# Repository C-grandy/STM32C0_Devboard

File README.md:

# STM32C0_Devboard
A devboard for the STM32C031

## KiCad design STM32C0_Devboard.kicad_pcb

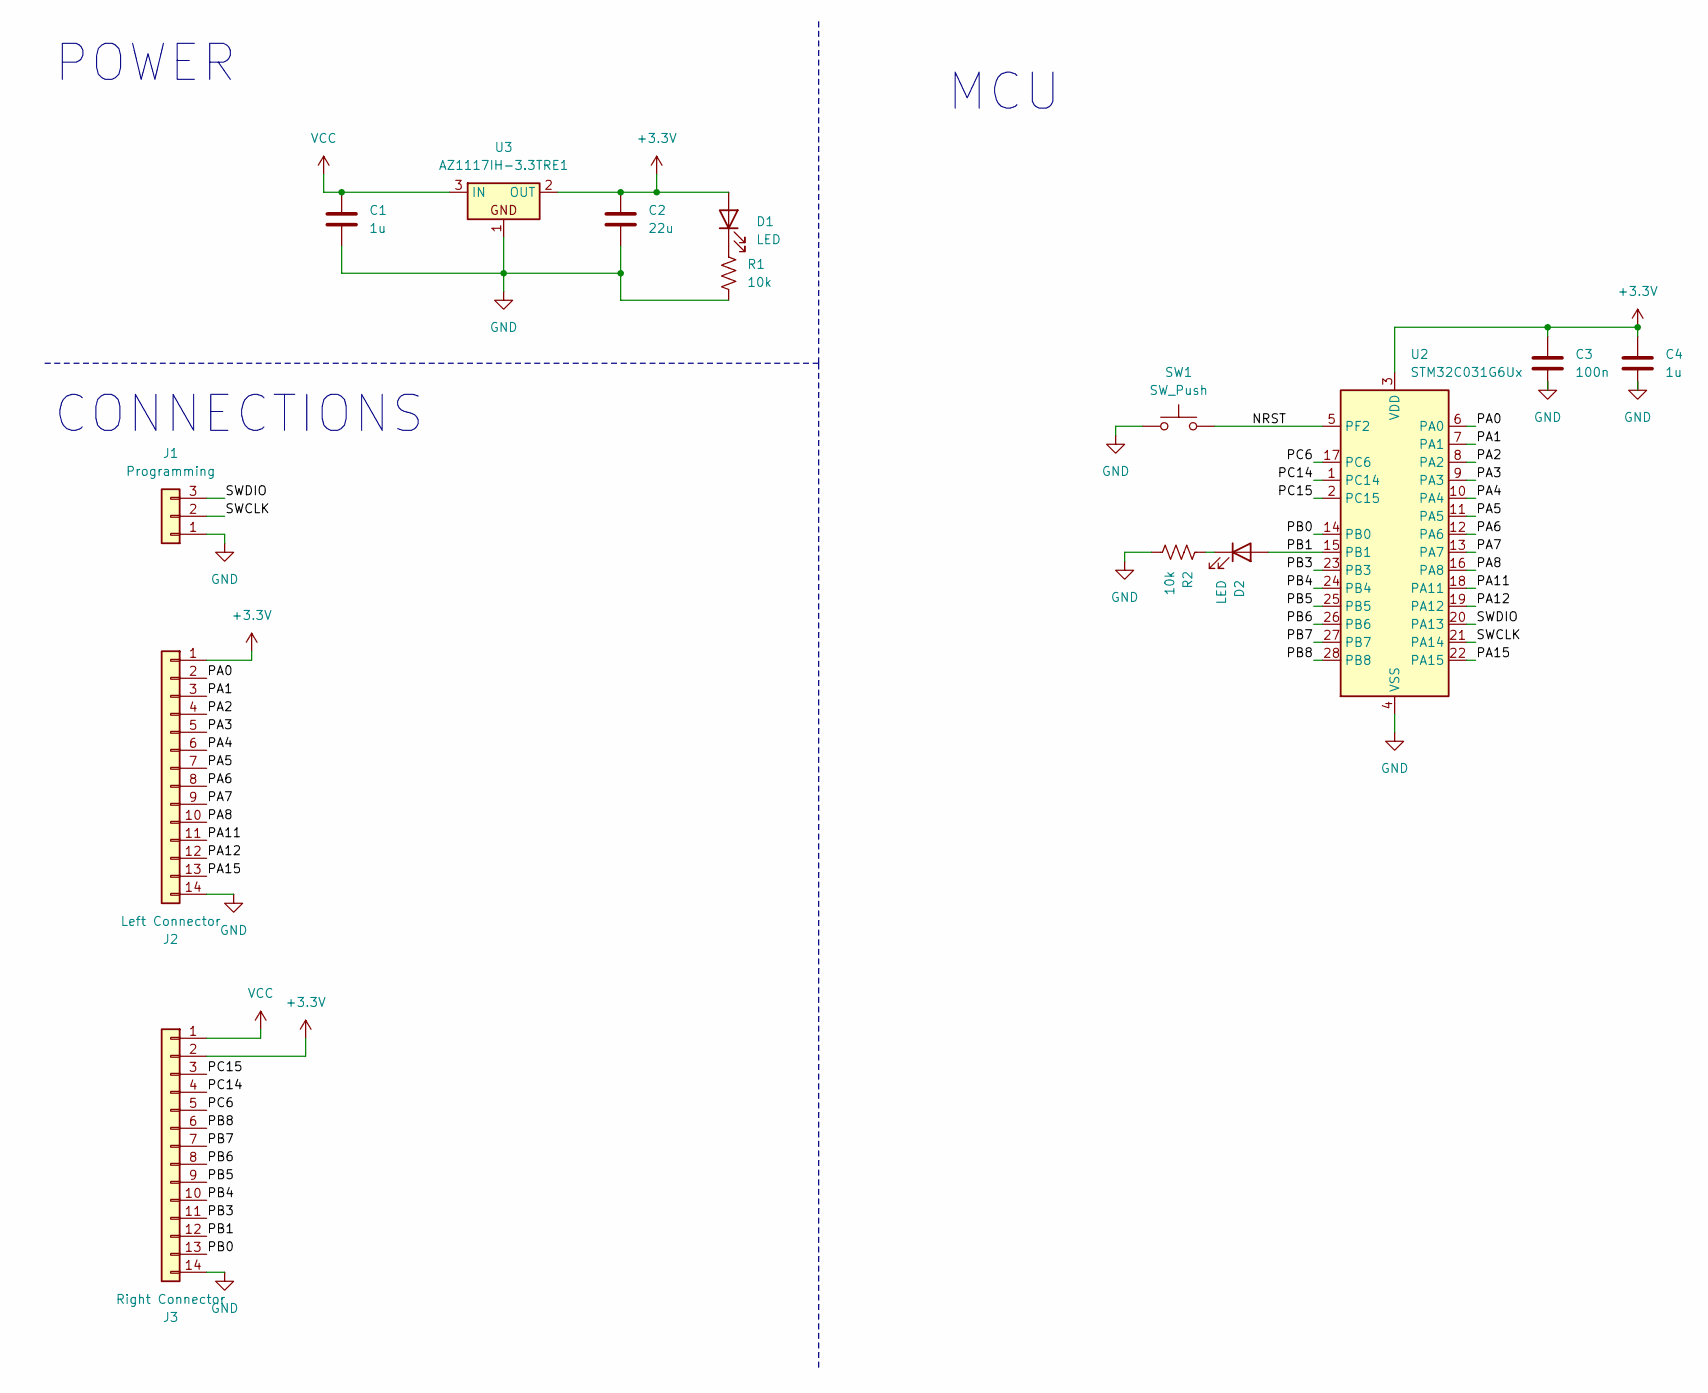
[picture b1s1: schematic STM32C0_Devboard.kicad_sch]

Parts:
C1, C4: 1u; C_0603_1608Metric
C2: 22u; C_0603_1608Metric
C3: 100n; C_0603_1608Metric
D1, D2: LED; LED_0603_1608Metric
J1: Programming; PinHeader_1x03_P2.54mm_Horizontal
J2: Left Connector; PinHeader_1x14_P2.54mm_Vertical
J3: Right Connector; PinHeader_1x14_P2.54mm_Vertical
R1, R2: 10k; R_0603_1608Metric
SW1: SW_Push; SW_Push_SPST_NO_Alps_SKRK; Part # PTS526SK15SMTR2 LFS
U2: STM32C031G6Ux; QFN-28_4x4mm_P0.5mm
U3: AZ1117IH-3.3TRE1; SOT-223-3_TabPin2

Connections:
+3.3V: C2.1, C3.1, C4.1, D1.2 (A), J2.1, J3.2, U2.3 (VDD), U3.2 (OUT)
/NRST: SW1.2, U2.5 (PF2)
/PA0: J2.2, U2.6 (PA0)
/PA1: J2.3, U2.7 (PA1)
/PA2: J2.4, U2.8 (PA2)
/PA3: J2.5, U2.9 (PA3)
/PA4: J2.6, U2.10 (PA4)
/PA5: J2.7, U2.11 (PA5)
/PA6: J2.8, U2.12 (PA6)
/PA7: J2.9, U2.13 (PA7)
/PA8: J2.10, U2.16 (PA8)
/PA11: J2.11, U2.18 (PA11)
/PA12: J2.12, U2.19 (PA12)
/PA15: J2.13, U2.22 (PA15)
/PB0: J3.13, U2.14 (PB0)
/PB1: D2.2 (A), J3.12, U2.15 (PB1)
/PB3: J3.11, U2.23 (PB3)
/PB4: J3.10, U2.24 (PB4)
/PB5: J3.9, U2.25 (PB5)
/PB6: J3.8, U2.26 (PB6)
/PB7: J3.7, U2.27 (PB7)
/PB8: J3.6, U2.28 (PB8)
/PC6: J3.5, U2.17 (PC6)
/PC14: J3.4, U2.1 (PC14)
/PC15: J3.3, U2.2 (PC15)
/SWCLK: J1.2, U2.21 (PA14)
/SWDIO: J1.3, U2.20 (PA13)
GND: C1.2, C2.2, C3.2, C4.2, J1.1, J2.14, J3.14, R1.2, R2.2, SW1.1, U2.4 (VSS), U3.1
unnamed: D1.1 (K), R1.1
unnamed: D2.1 (K), R2.1
VCC: C1.1, J3.1, U3.3 (IN)

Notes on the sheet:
POWER
CONNECTIONS
MCU

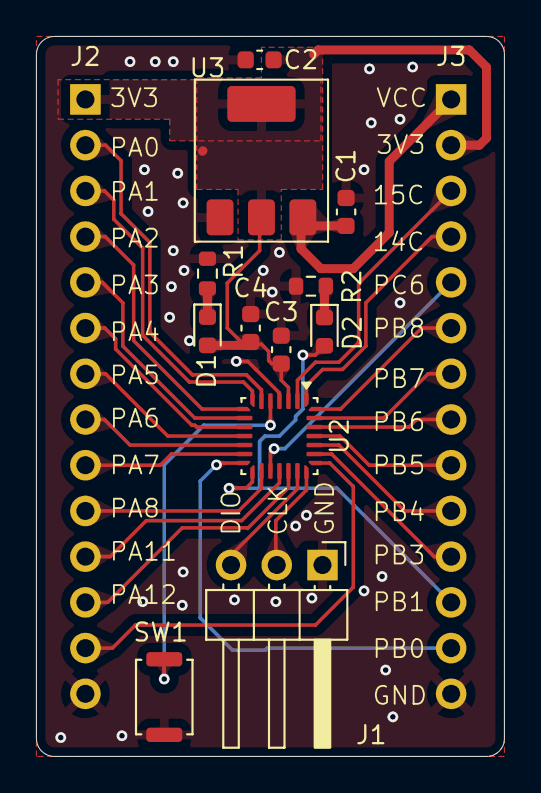
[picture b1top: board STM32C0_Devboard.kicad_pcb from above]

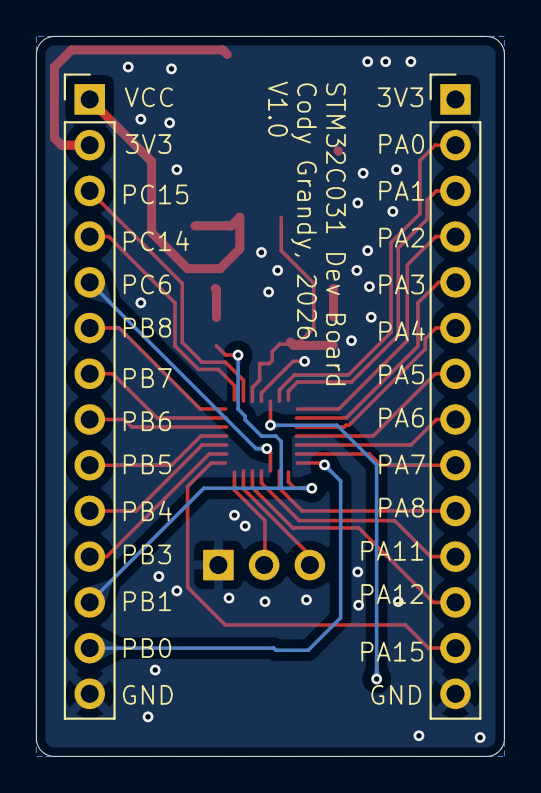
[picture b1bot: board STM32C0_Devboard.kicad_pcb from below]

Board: 2 copper layers, 26.0 x 40.0 mm, 14 parts (2 on the bottom side), 31 nets.

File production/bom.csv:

Designator,Footprint,Quantity,Value,LCSC Part #
"C1, C4",0603,2,1u,
C2,0603,1,22u,
C3,0603,1,100n,
"D1, D2",0603,2,LED,
J1,PinHeader_1x03_P2.54mm_Horizontal,1,Programming,
J2,PinHeader_1x14_P2.54mm_Vertical,1,Left Connector,
J3,PinHeader_1x14_P2.54mm_Vertical,1,Right Connector,
"R1, R2",0603,2,10k,
SW1,SW_Push_SPST_NO_Alps_SKRK,1,SW_Push,
U2,QFN-28_4x4mm_P0.5mm,1,STM32C031G6Ux,
U3,SOT-223-3_TabPin2,1,AZ1117IH-3.3TRE1,
